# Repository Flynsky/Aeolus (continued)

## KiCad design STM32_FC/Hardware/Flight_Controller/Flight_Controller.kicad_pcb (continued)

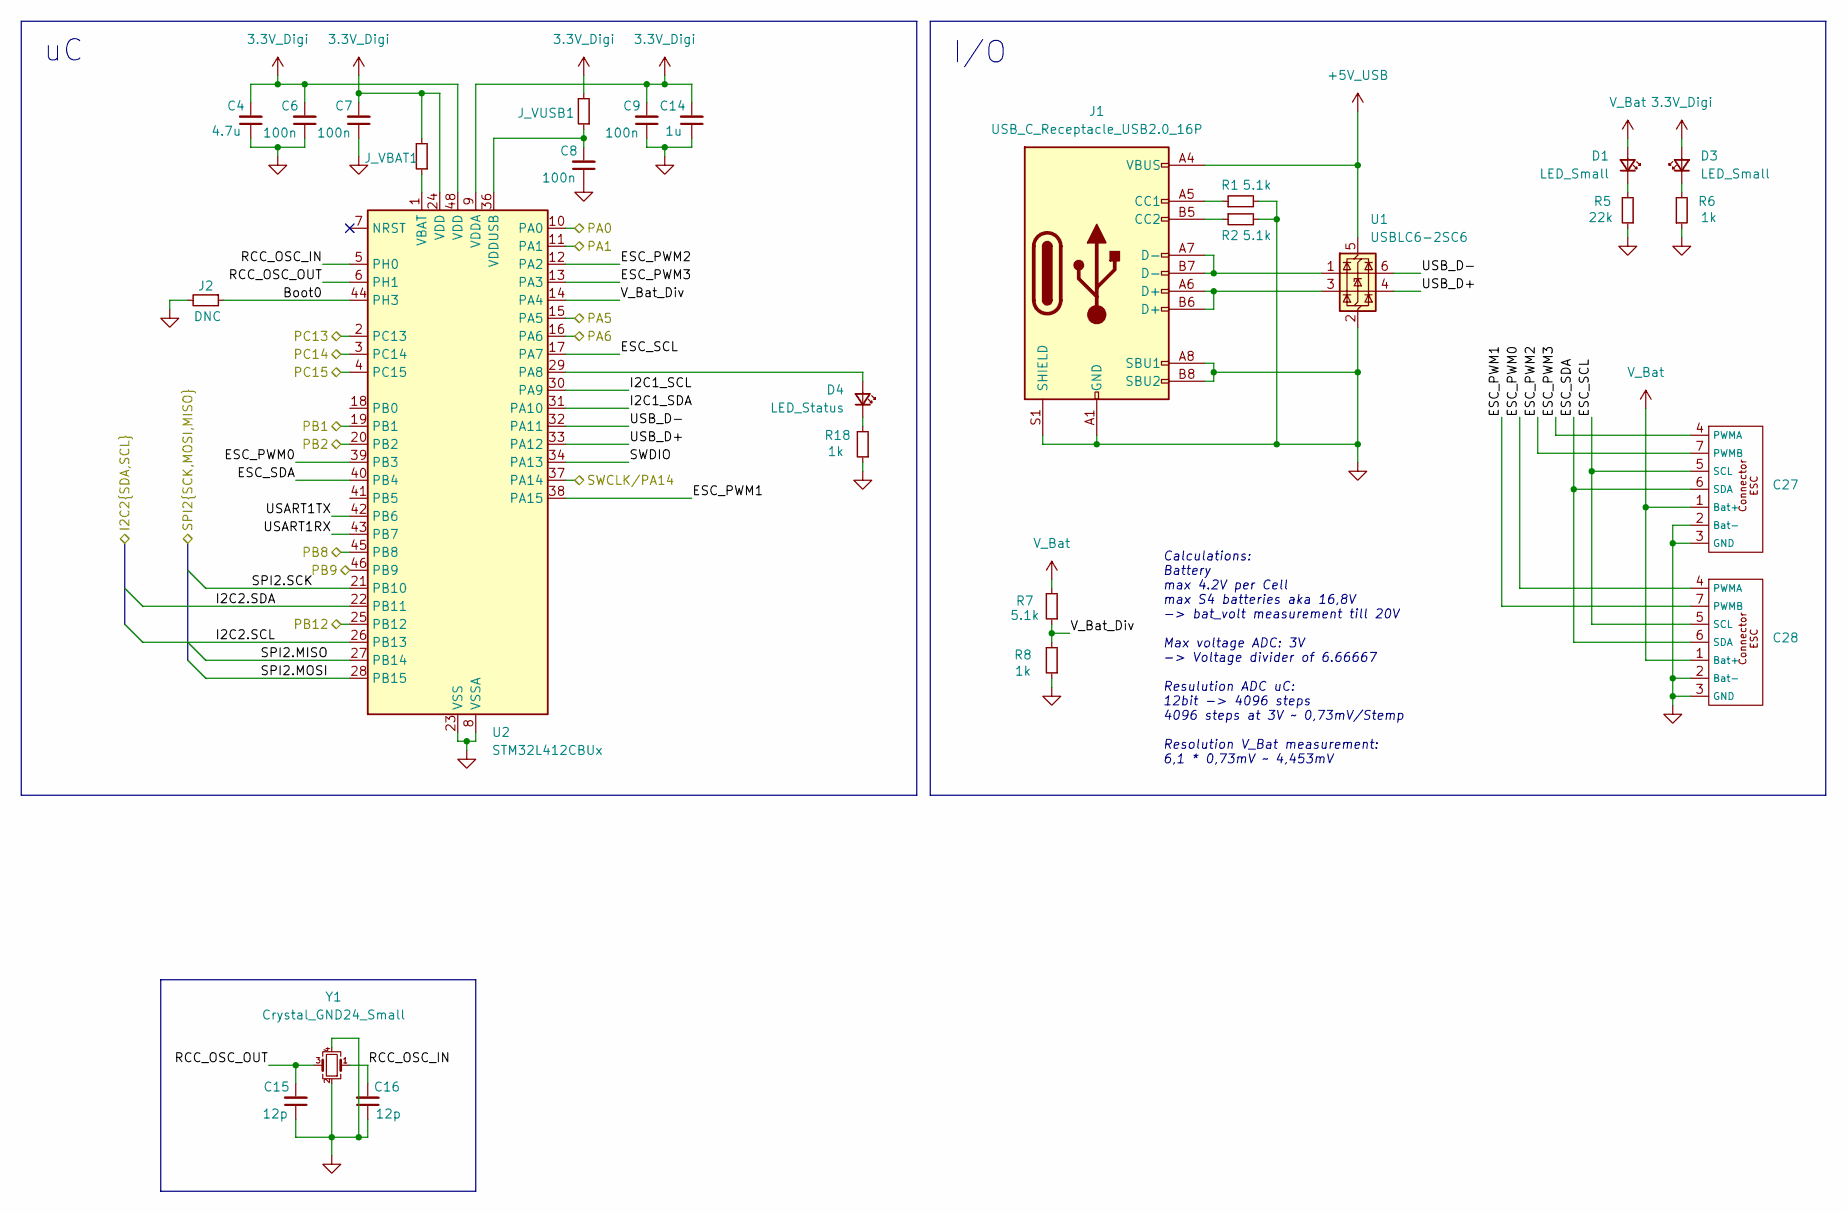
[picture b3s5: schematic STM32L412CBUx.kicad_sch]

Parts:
C4: 4.7u; C_0603_1608Metric
C6, C7, C8, C9: 100n; C_0402_1005Metric
C14: 1u; C_0603_1608Metric
C15, C16: 12p; C_0402_1005Metric
C27, C28: Connector_ESC_FC
D1, D3: LED_Small; LED_0603_1608Metric
D4: LED_Status; LED_0603_1608Metric
J1: USB_C_Receptacle_USB2.0_16P; GSB1C41110SSHR
J2: DNC; R_0603_1608Metric
J_VBAT1: 0; R_0603_1608Metric
J_VUSB1: 0; R_0603_1608Metric
R1, R2, R7: 5.1k; R_0603_1608Metric
R5: 22k; R_0603_1608Metric
R6, R8, R18: 1k; R_0603_1608Metric
U1: USBLC6-2SC6; SOT-23-6
U2: STM32L412CBUx; QFN-48-1EP_7x7mm_P0.5mm_EP5.6x5.6mm
Y1: Crystal_GND24_Small; ABM8W480000MHZ6D1XT3

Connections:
3.3V_Digi: C4.2, C6.2, C7.2, C9.2, C14.2, D3.2 (A), J_VBAT1.2, J_VUSB1.2, U2.9 (VDDA), U2.24 (VDD), U2.48 (VDD); also elsewhere on the board
+5V_USB: J1.A4 (VBUS), J1.A9 (VBUS), J1.B4 (VBUS), J1.B9 (VBUS), U1.5 (VBUS); also elsewhere on the board
/Com/CE_NRF: U2.4 (PC15); also elsewhere on the board
/Com/CS_NRF: U2.3 (PC14); also elsewhere on the board
/Com/IRQ_NRF: U2.2 (PC13); also elsewhere on the board
/Com/NR_SPI.MISO: U2.27 (PB14); also elsewhere on the board
/Com/NR_SPI.MOSI: U2.28 (PB15); also elsewhere on the board
/Com/NR_SPI.SCK: U2.21 (PB10); also elsewhere on the board
/STM32L412CBUx/Boot0: J2.1, U2.44 (PH3)
/STM32L412CBUx/ESC_PWM0: C28.4 (PWMA), U2.39 (PB3)
/STM32L412CBUx/ESC_PWM1: C28.7 (PWMB), U2.38 (PA15)
/STM32L412CBUx/ESC_PWM2: C27.7 (PWMB), U2.12 (PA2)
/STM32L412CBUx/ESC_PWM3: C27.4 (PWMA), U2.13 (PA3)
/STM32L412CBUx/ESC_SCL: C27.5 (SCL), C28.5 (SCL), U2.17 (PA7)
/STM32L412CBUx/ESC_SDA: C27.6 (SDA), C28.6 (SDA), U2.40 (PB4)
/STM32L412CBUx/I2C1_SCL: U2.30 (PA9)
/STM32L412CBUx/I2C1_SDA: U2.31 (PA10)
/STM32L412CBUx/PA0: U2.10 (PA0); also elsewhere on the board
/STM32L412CBUx/PA1: U2.11 (PA1); also elsewhere on the board
/STM32L412CBUx/PA5: U2.15 (PA5); also elsewhere on the board
/STM32L412CBUx/PA6: U2.16 (PA6); also elsewhere on the board
/STM32L412CBUx/PB1: U2.19 (PB1); also elsewhere on the board
/STM32L412CBUx/PB2: U2.20 (PB2); also elsewhere on the board
/STM32L412CBUx/PB8: U2.45 (PB8); also elsewhere on the board
/STM32L412CBUx/PB9: U2.46 (PB9); also elsewhere on the board
/STM32L412CBUx/PB12: U2.25 (PB12); also elsewhere on the board
/STM32L412CBUx/RCC_OSC_IN: C16.2, U2.5 (PH0), Y1.1
/STM32L412CBUx/RCC_OSC_OUT: C15.2, U2.6 (PH1), Y1.3
/STM32L412CBUx/SWCLK/PA14: U2.37 (PA14); also elsewhere on the board
/STM32L412CBUx/SWDIO: U2.34 (PA13)
/STM32L412CBUx/USART1RX: U2.43 (PB7)
/STM32L412CBUx/USART1TX: U2.42 (PB6)
/STM32L412CBUx/USB_D+: U1.4 (I/O2), U2.33 (PA12)
/STM32L412CBUx/USB_D-: U1.6 (I/O1), U2.32 (PA11)
/STM32L412CBUx/V_Bat_Div: R7.1, R8.2, U2.14 (PA4)
GND: C4.1, C6.1, C7.1, C8.1, C9.1, C14.1, C15.1, C16.1, C27.2 (Bat-), C27.3 (GND), C28.2 (Bat-), C28.3 (GND), J1.A1 (GND), J1.A8 (SBU1), J1.A12 (GND), J1.B1 (GND), J1.B8 (SBU2), J1.B12 (GND), J1.S1 (SHIELD), J2.2, R1.2, R2.2, R5.1, R6.1, R8.1, R18.1, U1.2 (GND), U2.8 (VSSA), U2.23 (VSS), U2.35 (VSS), U2.47 (VSS), U2.49 (VSS), Y1.2, Y1.4; also elsewhere on the board
unnamed: D1.1 (K), R5.2
unnamed: D3.1 (K), R6.2
unnamed: D4.2 (A), U2.29 (PA8)
unnamed: D4.1 (K), R18.2
unnamed: J1.A5 (CC1), R1.1
unnamed: J1.B5 (CC2), R2.1
unnamed: J1.A6 (D+), J1.B6 (D+), U1.3 (I/O2)
unnamed: J1.A7 (D-), J1.B7 (D-), U1.1 (I/O1)
unnamed: J_VBAT1.1, U2.1 (VBAT)
unnamed: C8.2, J_VUSB1.1, U2.36 (VDDUSB)
V_Bat: C27.1 (Bat+), C28.1 (Bat+), D1.2 (A), R7.2; also elsewhere on the board

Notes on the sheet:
Calculations: Battery max 4.2V per Cell max S4 batteries aka 16,8V -> bat_volt measurement till 20V Max voltage ADC: 3V -> Voltage divider of 6.66667 Resulution ADC uC: 12bit -> 4096 steps 4096 steps at 3V ~ 0,73mV/Stemp Resolution V_Bat measurement: 6,1 * 0,73mV ~ 4,453mV
I/O

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
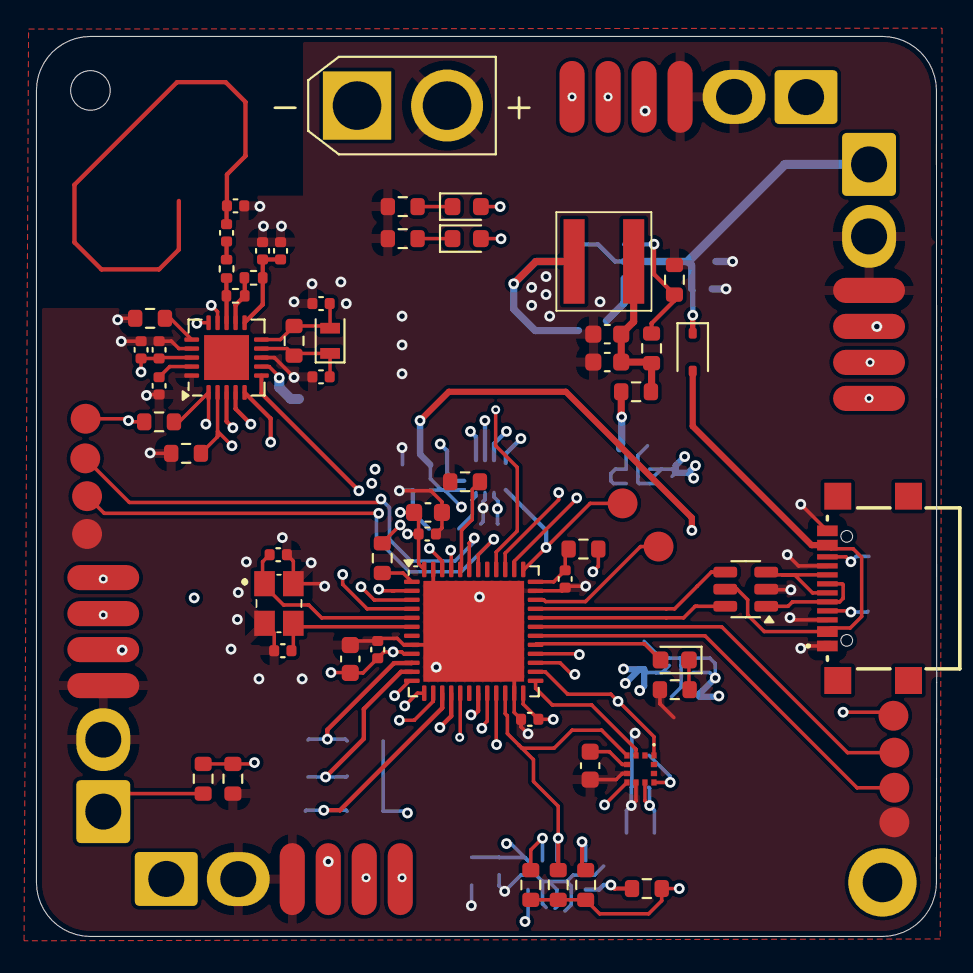
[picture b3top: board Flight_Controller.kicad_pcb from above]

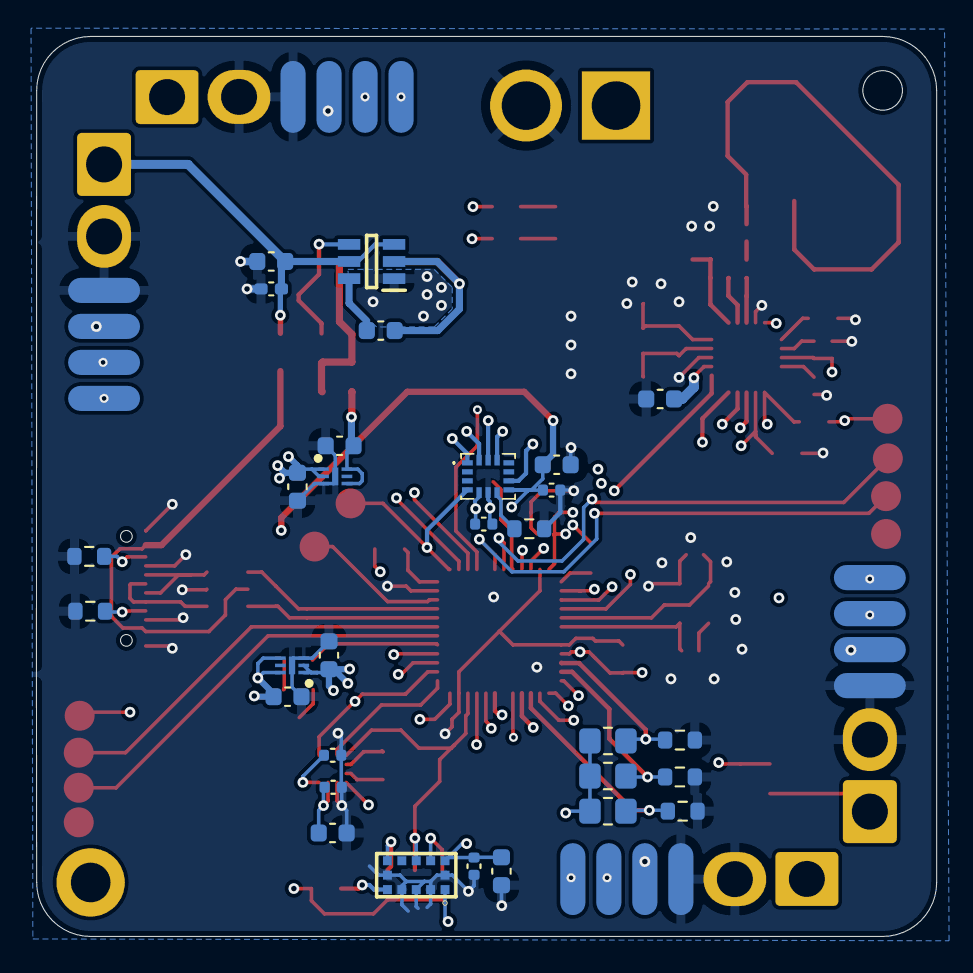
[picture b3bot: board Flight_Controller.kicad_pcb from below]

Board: 4 copper layers, 50.0 x 50.0 mm, 89 parts (30 on the bottom side), 61 nets.

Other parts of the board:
U5: NRF24L01; QFN-20-1EP_4x4mm_P0.5mm_EP2.5x2.5mm
Y2: 16MHz; Crystal_SMD_2012-2Pin_2.0x1.2mm

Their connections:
3.3V_Digi: U5.7 (VDD), U5.15 (VDD), U5.18 (VDD); also elsewhere on the board
/Com/CE_NRF: U5.1 (CE); also elsewhere on the board
/Com/CS_NRF: U5.2 (CSN); also elsewhere on the board
/Com/IRQ_NRF: U5.6 (IRQ); also elsewhere on the board
/Com/NR_SPI.MISO: U5.5 (MISO); also elsewhere on the board
/Com/NR_SPI.MOSI: U5.4 (MOSI); also elsewhere on the board
/Com/NR_SPI.SCK: U5.3 (SCK); also elsewhere on the board
GND: U5.8 (VSS), U5.14 (VSS), U5.17 (VSS), U5.20 (VSS); also elsewhere on the board
unnamed 56: U5.12 (ANT1); also elsewhere on the board
unnamed 57: U5.13 (ANT2); also elsewhere on the board
unnamed 58: U5.19 (DVDD); also elsewhere on the board
unnamed 59: U5.16 (IREF); also elsewhere on the board
unnamed 60: U5.11 (VDD_PA); also elsewhere on the board
unnamed 61: U5.10 (XC1), Y2.2; also elsewhere on the board
unnamed 62: U5.9 (XC2), Y2.1; also elsewhere on the board

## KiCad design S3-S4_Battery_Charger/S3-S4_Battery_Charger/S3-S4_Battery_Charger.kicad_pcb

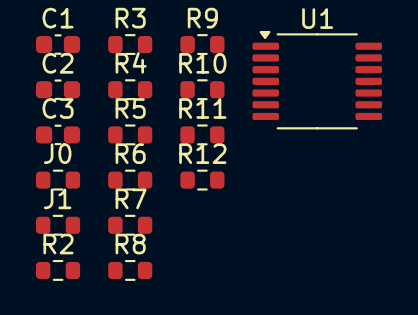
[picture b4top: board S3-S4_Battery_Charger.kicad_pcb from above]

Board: 2 copper layers, 17 parts (0 on the bottom side), 12 nets, no tracks yet.

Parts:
C1, C2, C3: DNP; C_0603_1608Metric
J0: 0; R_0603_1608Metric
J1: DNP; R_0603_1608Metric
R2, R3: R_Small; R_0603_1608Metric
R4, R5, R7, R9, R11: 100; R_0603_1608Metric
R6, R8, R10: 100k; R_0603_1608Metric
R12: 10k; R_0603_1608Metric
U1: Opamp_Quad; TSSOP-14_4.4x5mm_P0.65mm

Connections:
/V_Curr: C1.1, U1.6 (-)
/V_out: C3.1, R12.1, U1.2 (-)
GND: C1.2, C3.2, R8.2, R10.2
unnamed: C2.1, R4.2, R5.1, R6.1, U1.8
unnamed: R7.1, R8.1
unnamed: C2.2, J0.2, R6.2, U1.7
unnamed: J1.2, R7.2
unnamed: R9.2, R10.1
unnamed: R12.2, U1.12 (+)
unnamed: R9.1, R11.2, U1.14
unnamed: R3.1, U1.5 (+)
unnamed: J0.1, U1.9 (-)

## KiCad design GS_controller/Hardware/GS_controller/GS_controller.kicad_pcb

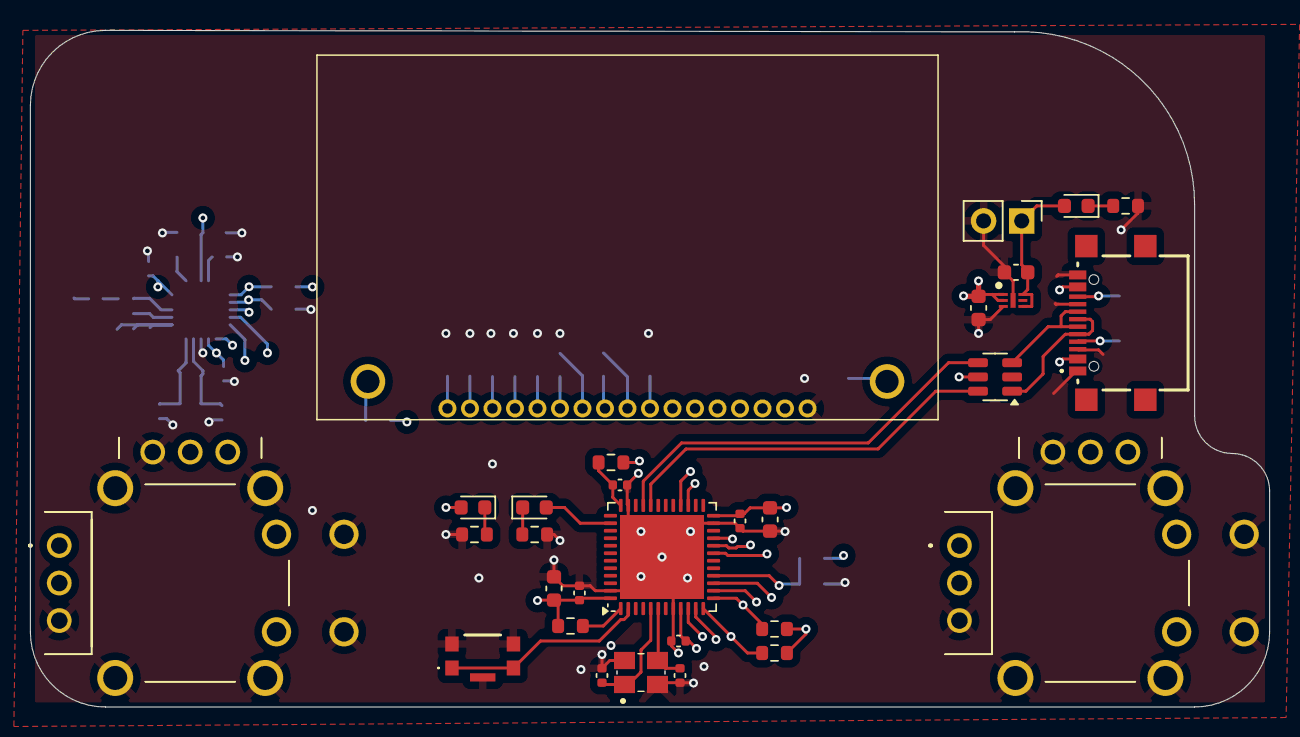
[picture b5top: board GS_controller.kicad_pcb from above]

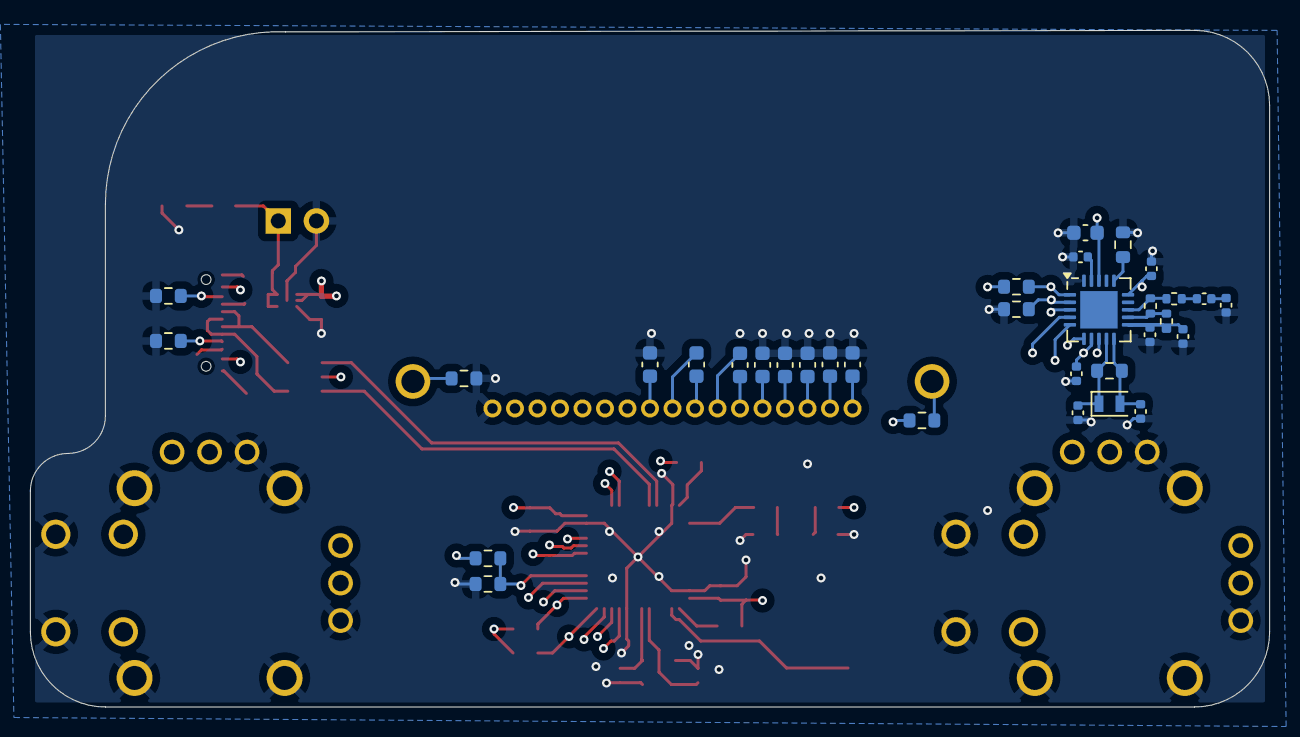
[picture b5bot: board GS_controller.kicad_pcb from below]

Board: 4 copper layers, 82.6 x 45.1 mm, 63 parts (33 on the bottom side), 49 nets.

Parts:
BT1: Battery; PinHeader_1x02_P2.54mm_Vertical
C1, C2: 2u2/10V/X5; C_0603_1608Metric
C3: 4.7u DNP; C_0603_1608Metric
C4: 4.7u; C_0603_1608Metric
C5: 1n; C_0402_1005Metric
C6, C7, C8, C9: 100n; C_0402_1005Metric
C10: 33n; C_0402_1005Metric
C11: 10n; C_0402_1005Metric
C12, C13: 22p; C_0402_1005Metric
C14, C21, C24, C25, C26, C27: 1u; C_0603_1608Metric
C15, C16: TODO; C_0402_1005Metric
C17: 1.5p; C_0402_1005Metric
C18: 1p; C_0402_1005Metric
C19: 2.2n; C_0402_1005Metric
C20: 4.7p; C_0402_1005Metric
C22, C23, C28: 2.2u; C_0603_1608Metric
D1, D3: LED_Small; LED_0603_1608Metric
D2: LED_Status; LED_0603_1608Metric
DS1: NHD-C12832A1Z-FSW-FBW-3V3; NHDC12832A1ZFSWFBW3V3
IC1: MIC5528-3.3YMT-TR; SON40P120X120X60-7N-D
J0, J2: 0; R_0603_1608Metric
J1: USB_C_Receptacle_USB2.0_16P; GSB1C41110SSHR
J_VBAT1: 0; R_0603_1608Metric
J_VUSB1: 0; R_0603_1608Metric
L1: 8.2n; R_0402_1005Metric
L2: 2.7n; R_0402_1005Metric
L3: 3.9n; R_0402_1005Metric
R1, R2: 5.1k; R_0603_1608Metric
R3, R4, R5: 10k; R_0603_1608Metric
R6, R7, R8, R18: TODO; R_0603_1608Metric
R9: 22k; R_0603_1608Metric
R10, R11, R12: 1M; R_0603_1608Metric
S1, S2: THB001P
S3: 435441019830
U1: USBLC6-2SC6; SOT-23-6
U2: STM32L412CBUx; QFN-48-1EP_7x7mm_P0.5mm_EP5.6x5.6mm
U3: NRF24L01; QFN-20-1EP_4x4mm_P0.5mm_EP2.5x2.5mm
Y1: Crystal_GND24_Small; ABM8W480000MHZ6D1XT3
Y2: 16MHz; Crystal_SMD_2012-2Pin_2.0x1.2mm

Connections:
3.3V_Digi: C2.2, C3.2, C4.2, C5.2, C6.2, C7.2, C9.2, C11.2, C14.2, D3.2 (A), DS1.12 (VDD), IC1.1 (VOUT_1), IC1.2 (VOUT_2), J0.1, J_VBAT1.2, J_VUSB1.2, R4.1, R11.1, R12.1, S1.1, S1.11 (1'), S2.1, S2.11 (1'), U2.9 (VDDA), U2.24 (VDD), U2.48 (VDD), U3.7 (VDD), U3.15 (VDD), U3.18 (VDD)
+5V_USB: J1.A4 (VBUS), J1.A9 (VBUS), U1.5 (VBUS)
/50 OhmRF I/O: C17.2, C18.1
/A_0: S1.2, U2.10 (PA0)
/A_1: S1.12 (2'), U2.11 (PA1)
/A_2: R11.2, S1.A1 (COM_1), S1.B1 (COM_2), U2.12 (PA2)
/B_0: S2.2, U2.14 (PA4)
/B_1: S2.12 (2'), U2.15 (PA5)
/B_2: R12.2, S2.A1 (COM_1), S2.B1 (COM_2), U2.13 (PA3)
/CE_NRF: R4.2, U3.1 (CE)
/CS_NRF: R3.1, U3.2 (CSN)
/Controller/PB1: DS1.16 (/RES), U2.19 (PB1)
/Controller/PB2: DS1.15 (A0), U2.20 (PB2)
/Controller/RCC_OSC_IN: C16.2, U2.5 (PH0), Y1.1
/Controller/RCC_OSC_OUT: C15.2, U2.6 (PH1), Y1.3
/Controller/SPI2.MISO: U2.27 (PB14), U3.5 (MISO)
/Controller/SPI2.MOSI: DS1.13 (SI), U2.28 (PB15), U3.4 (MOSI)
/Controller/SPI2.SCK: DS1.14 (SCL), U2.21 (PB10), U3.3 (SCK)
/Controller/USB_D+: U1.4 (I/O2), U2.33 (PA12)
/Controller/USB_D-: U1.6 (I/O1), U2.32 (PA11)
/Controller/V_Bat_Div: R7.1, R8.2, U2.16 (PA6)
GND: BT1.2 (-), C1.1, C2.1, C3.1, C4.1, C5.1, C6.1, C7.1, C8.1, C9.1, C10.1, C11.1, C12.1, C13.1, C14.1, C15.1, C16.1, C18.2, C19.1, C20.2, C21.1, C24.1, C25.1, C26.1, C27.1, C28.1, DS1.11 (VSS), DS1.17 (CS1B), IC1.3 (GND), IC1.7 (EP), J1.A1 (GND), J1.A8 (SBU1), J1.A12 (GND), J1.B8 (SBU2), J2.2, R1.2, R2.2, R3.2, R5.1, R6.1, R8.1, R9.2, R18.1, S1.3, S1.13 (3'), S1.C1 (NO_1), S1.D1 (NO_2), S1.MH1, S1.MH2, S1.MH3, S1.MH4, S2.3, S2.13 (3'), S2.C1 (NO_1), S2.D1 (NO_2), S2.MH1, S2.MH2, S2.MH3, S2.MH4, S3.2 (COM_1), S3.3 (COM_2), S3.G1 (GND), U1.2 (GND), U2.8 (VSSA), U2.23 (VSS), U2.35 (VSS), U2.47 (VSS), U2.49 (VSS), U3.8 (VSS), U3.14 (VSS), U3.17 (VSS), U3.20 (VSS), Y1.2, Y1.4
unnamed: C8.2, J_VUSB1.1, U2.36 (VDDUSB)
unnamed: C17.1, L3.2
unnamed: D1.1 (K), R5.2
unnamed: D3.1 (K), R6.2
unnamed: C23.2, DS1.8 (C1+)
unnamed: C23.1, DS1.9 (C1-)
unnamed: C22.1, DS1.7 (C2+)
unnamed: C22.2, DS1.6 (C2-)
unnamed: DS1.MH1, J0.2
unnamed: DS1.MH2, J2.1
unnamed: C27.2, DS1.1 (V0)
unnamed: C26.2, DS1.2 (V1)
unnamed: C25.2, DS1.3 (V2)
unnamed: C24.2, DS1.4 (V3)
unnamed: C21.2, DS1.5 (V4)
unnamed: C28.2, DS1.10 (VOUT)
unnamed: J1.A6 (D+), J1.B6 (D+), U1.3 (I/O2)
unnamed: J1.A7 (D-), J1.B7 (D-), U1.1 (I/O1)
unnamed: S3.1 (NO_1), S3.4 (NO_2), U2.2 (PC13)
unnamed: L1.1, L2.2, U3.12 (ANT1)
unnamed: L1.2, L3.1, U3.13 (ANT2)
unnamed: C10.2, U3.19 (DVDD)
unnamed: R9.1, U3.16 (IREF)
unnamed: C19.2, C20.1, L2.1, U3.11 (VDD_PA)
unnamed: C13.2, R10.1, U3.10 (XC1), Y2.2
unnamed: C12.2, R10.2, U3.9 (XC2), Y2.1
V_Bat: BT1.1 (+), C1.2, D1.2 (A), IC1.4 (EN), IC1.6 (VIN), R7.2

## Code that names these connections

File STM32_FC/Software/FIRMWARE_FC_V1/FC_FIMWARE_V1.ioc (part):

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Mcu.Name=STM32L412CBUx
Mcu.Package=UFQFPN48
Mcu.UserName=STM32L412CBUx
PA0.GPIOParameters=GPIO_Label
PA0.GPIO_Label=PIN_NTC_0
PA0.Signal=ADCx_IN5
PA1.GPIOParameters=GPIO_Label
PA1.GPIO_Label=PIN_NTC_1
PA1.Signal=ADCx_IN6
PA10.Mode=I2C
PA10.Signal=I2C1_SDA
PA11.Mode=Device
PA11.Signal=USB_DM
PA12.Mode=Device
PA12.Signal=USB_DP
PA13\ (JTMS/SWDIO).Mode=Serial_Wire
PA13\ (JTMS/SWDIO).Signal=SYS_JTMS-SWDIO
PA14\ (JTCK/SWCLK).GPIOParameters=GPIO_Label
PA14\ (JTCK/SWCLK).GPIO_Label=PIN_IMU_INT1
PA14\ (JTCK/SWCLK).Mode=Serial_Wire
PA14\ (JTCK/SWCLK).Signal=SYS_JTCK-SWCLK
PA4.GPIOParameters=GPIO_Label
PA4.GPIO_Label=PIN_V_BAT_DIV
PA4.Signal=ADCx_IN9
PA5.GPIOParameters=GPIO_Label
PA5.GPIO_Label=PIN_NTC_2
PA5.Signal=ADCx_IN10
PA6.GPIOParameters=GPIO_Label
PA6.GPIO_Label=PIN_TOF_X_SHUNT
PA6.Signal=GPIO_Output
PA7.Mode=I2C
PA7.Signal=I2C3_SCL
PA8.GPIOParameters=GPIO_Label
PA8.GPIO_Label=PIN_STATUS_LED
PA8.Signal=GPIO_Output
PA9.Mode=I2C
PA9.Signal=I2C1_SCL
PB1.GPIOParameters=GPIO_Label
PB1.GPIO_Label=PIN_TOF_INT
PB1.Signal=GPIO_Input
PB10.Mode=Full_Duplex_Master
PB10.Signal=SPI2_SCK
PB11.Mode=I2C
PB11.Signal=I2C2_SDA
PB12.GPIOParameters=GPIO_Label
PB12.GPIO_Label=PIN_MAG_CS
PB12.Signal=GPIO_Output
PB13.Mode=I2C
PB13.Signal=I2C2_SCL
PB14.Mode=Full_Duplex_Master
PB14.Signal=SPI2_MISO
PB15.Mode=Full_Duplex_Master
PB15.Signal=SPI2_MOSI
PB2.GPIOParameters=GPIO_Label
PB2.GPIO_Label=PIN_MAG_INT
PB2.Signal=GPIO_Input
PB4\ (NJTRST).Mode=I2C
PB4\ (NJTRST).Signal=I2C3_SDA
PB8.GPIOParameters=GPIO_Label
PB8.GPIO_Label=PIN_IMU_INT2
PB8.Signal=GPIO_Input
PB9.GPIOParameters=GPIO_Label
PB9.GPIO_Label=PIN_IMU_CS
PB9.Signal=GPIO_Output
PC13.GPIOParameters=GPIO_Label
PC13.GPIO_Label=PIN_IRQ_NRF
PC13.Signal=GPIO_Input
PC14-OSC32_IN\ (PC14).GPIOParameters=GPIO_Label
PC14-OSC32_IN\ (PC14).GPIO_Label=PIN_CS_NRF
PC14-OSC32_IN\ (PC14).Signal=GPIO_Output
PC15-OSC32_OUT\ (PC15).GPIOParameters=GPIO_Label
PC15-OSC32_OUT\ (PC15).GPIO_Label=PIN_CE_NRF
PC15-OSC32_OUT\ (PC15).Signal=GPIO_Output
PH0-OSC_IN\ (PH0).Mode=HSE-External-Oscillator
PH0-OSC_IN\ (PH0).Signal=RCC_OSC_IN
PH1-OSC_OUT\ (PH1).Mode=HSE-External-Oscillator
PH1-OSC_OUT\ (PH1).Signal=RCC_OSC_OUT
RCC.HSE_VALUE=12000000
RCC.SYSCLKFreq_VALUE=80000000
RCC.SYSCLKSource=RCC_SYSCLKSOURCE_PLLCLK
board=custom

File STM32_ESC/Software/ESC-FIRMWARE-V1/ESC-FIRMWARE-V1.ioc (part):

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Mcu.Name=STM32L412CBUx
Mcu.Package=UFQFPN48
Mcu.UserName=STM32L412CBUx
PA0.GPIOParameters=GPIO_Label
PA0.GPIO_Label=PIN_VV_Sense_C
PA0.Signal=ADCx_IN5
PA1.GPIOParameters=GPIO_Label
PA1.GPIO_Label=PIN_VI_Sense_C
PA1.Signal=ADCx_IN6
PA10.Mode=I2C
PA10.Signal=I2C1_SDA
PA11.Mode=Device
PA11.Signal=USB_DM
PA12.Mode=Device
PA12.Signal=USB_DP
PA13\ (JTMS/SWDIO).Mode=Serial_Wire
PA13\ (JTMS/SWDIO).Signal=SYS_JTMS-SWDIO
PA14\ (JTCK/SWCLK).Mode=Serial_Wire
PA14\ (JTCK/SWCLK).Signal=SYS_JTCK-SWCLK
PA2.GPIOParameters=GPIO_Label
PA2.GPIO_Label=PIN_VV_Sense_B
PA2.Signal=ADCx_IN7
PA3.GPIOParameters=GPIO_Label
PA3.GPIO_Label=PIN_VI_Sense_B
PA3.Signal=ADCx_IN8
PA4.GPIOParameters=GPIO_Label
PA4.GPIO_Label=PIN_VV_Sense_A
PA4.Signal=ADCx_IN9
PA5.GPIOParameters=GPIO_Label
PA5.GPIO_Label=PIN_VI_Sense_A
PA5.Signal=ADCx_IN10
PA6.GPIOParameters=GPIO_Label
PA6.GPIO_Label=V_BAT_DIV
PA6.Signal=ADCx_IN11
PA7.GPIOParameters=GPIO_Label
PA7.GPIO_Label=PIN_LO_A
PA7.Mode=PWM Generation1 CH1 CH1N
PA7.Signal=TIM1_CH1N
PA8.GPIOParameters=GPIO_Label
PA8.GPIO_Label=PIN_HI_A
PA8.Signal=S_TIM1_CH1
PA9.Mode=I2C
PA9.Signal=I2C1_SCL
PH0-OSC_IN\ (PH0).Mode=HSE-External-Oscillator
PH0-OSC_IN\ (PH0).Signal=RCC_OSC_IN
PH1-OSC_OUT\ (PH1).Mode=HSE-External-Oscillator
PH1-OSC_OUT\ (PH1).Signal=RCC_OSC_OUT
RCC.HSE_VALUE=12000000
RCC.SYSCLKFreq_VALUE=80000000
RCC.SYSCLKSource=RCC_SYSCLKSOURCE_PLLCLK
board=custom

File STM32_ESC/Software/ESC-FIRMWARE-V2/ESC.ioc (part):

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Mcu.Name=STM32L412CBUx
Mcu.Package=UFQFPN48
Mcu.UserName=STM32L412CBUx
PA0.GPIOParameters=GPIO_PuPd,GPIO_Mode
PA0.GPIO_Mode=GPIO_MODE_ANALOG_ADC_CONTROL
PA0.GPIO_PuPd=GPIO_NOPULL
PA0.Signal=ADCx_IN5
PA1.GPIOParameters=GPIO_PuPd,GPIO_Mode
PA1.GPIO_Mode=GPIO_MODE_ANALOG_ADC_CONTROL
PA1.GPIO_PuPd=GPIO_NOPULL
PA1.Signal=ADCx_IN6
PA10.GPIOParameters=GPIO_Label
PA10.GPIO_Label=PIN_HI_C
PA10.Signal=S_TIM1_CH3
PA11.Mode=Device
PA11.Signal=USB_DM
PA12.Mode=Device
PA12.Signal=USB_DP
PA13\ (JTMS/SWDIO).Mode=Serial_Wire
PA13\ (JTMS/SWDIO).Signal=SYS_JTMS-SWDIO
PA14\ (JTCK/SWCLK).Mode=Serial_Wire
PA14\ (JTCK/SWCLK).Signal=SYS_JTCK-SWCLK
PA2.GPIOParameters=GPIO_PuPd,GPIO_Mode
PA2.GPIO_Mode=GPIO_MODE_ANALOG_ADC_CONTROL
PA2.GPIO_PuPd=GPIO_NOPULL
PA2.Signal=ADCx_IN7
PA3.GPIOParameters=GPIO_PuPd,GPIO_Mode
PA3.GPIO_Mode=GPIO_MODE_ANALOG_ADC_CONTROL
PA3.GPIO_PuPd=GPIO_NOPULL
PA3.Signal=ADCx_IN8
PA4.GPIOParameters=GPIO_PuPd,GPIO_Mode
PA4.GPIO_Mode=GPIO_MODE_ANALOG_ADC_CONTROL
PA4.GPIO_PuPd=GPIO_NOPULL
PA4.Signal=ADCx_IN9
PA5.GPIOParameters=GPIO_PuPd,GPIO_Mode
PA5.GPIO_Mode=GPIO_MODE_ANALOG_ADC_CONTROL
PA5.GPIO_PuPd=GPIO_NOPULL
PA5.Signal=ADCx_IN10
PA6.GPIOParameters=GPIO_PuPd,GPIO_Mode
PA6.GPIO_Mode=GPIO_MODE_ANALOG_ADC_CONTROL
PA6.GPIO_PuPd=GPIO_NOPULL
PA6.Signal=ADCx_IN11
PA7.GPIOParameters=GPIO_Label
PA7.GPIO_Label=PIN_LO_A
PA7.Mode=PWM Generation1 CH1 CH1N
PA7.Signal=TIM1_CH1N
PA8.GPIOParameters=GPIO_Label
PA8.GPIO_Label=PIN_HI_A
PA8.Signal=S_TIM1_CH1
PB1.GPIOParameters=GPIO_Label
PB1.GPIO_Label=PIN_LO_C
PB1.Mode=PWM Generation3 CH3 CH3N
PB1.Signal=TIM1_CH3N
PB8.Mode=I2C
PB8.Signal=I2C1_SCL
PB9.Mode=I2C
PB9.Signal=I2C1_SDA
PH0-OSC_IN\ (PH0).Mode=HSE-External-Oscillator
PH0-OSC_IN\ (PH0).Signal=RCC_OSC_IN
PH1-OSC_OUT\ (PH1).Mode=HSE-External-Oscillator
PH1-OSC_OUT\ (PH1).Signal=RCC_OSC_OUT
RCC.HSE_VALUE=12000000
RCC.SYSCLKFreq_VALUE=80000000
RCC.SYSCLKSource=RCC_SYSCLKSOURCE_PLLCLK
board=custom

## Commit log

2024-10-19 added current status
2024-10-19 add picture
2024-10-19 removed picture
2024-10-20 added boot resistor and made last minit changes
2024-10-20 added plotter
2024-10-20 work on gs_monitor
2024-10-24 got bytewise Serial Stream roughly working
2024-10-26 made order and started on cad
2024-11-02 updated order and gs.order got a nice boom and gs better structure and a cordinate system
2024-11-07 switched package managing to poetry
2024-11-10 restructuring of coder base and adding grafene suport
2024-11-15 added pictures
2024-11-15 changed name
2024-11-23 made stm32 software work in vscode
2024-12-01 added stm32 things
2024-12-21 reworked folder structure and added first steps of imu libary
2024-12-27 got communication to IMU working
2024-12-27 added integration to rotation and posision as well as teleplott
2024-12-27 added teleplot settings
2024-12-27 Add build directory to .gitignore
2024-12-27 removed build from git
2024-12-27 added us Timer
2024-12-28 minor changes in debugging
2024-12-29 started working on fifo
2025-01-01 added console
2025-01-05 reworked console to make it more clean
2025-02-05 added test data
2025-03-05 added kalman and dokumentation
2025-04-09 switch to linux
2025-04-09 new ESC version wooow baby
2025-04-09 V1.1
2025-04-12 new Console
2025-04-12 removed debug foöder
2025-04-22 made linux friednly. Also upt uner input on extra thread
2025-04-23 mess
2025-04-26 make crossplatform better
2025-04-26 added auto reconnect feature
2025-04-26 added cmake build and dfu upload/liost support to terminal
2025-04-26 refined terminal and CMAKE
2025-05-03 new try at an ESC
2026-05-01 new ESC revision
2026-05-01 .gitignore is now working
